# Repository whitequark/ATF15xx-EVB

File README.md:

ATF1502-EVB
===========

*ATF1502-EVB* is a simple and low-cost evaluation board for the [Microchip ATF1502AS](https://www.microchip.com/wwwproducts/en/ATF1502AS) CPLD. It may also be used with ATF1504AS in the TQFP-44 package. It breaks out every I/O pin on a DIP-style package, exposes JTAG on a 6-pin connector, and optionally (with a solder jumper) allows two LEDs to be connected to pins 22 and 23 of the CPLD.

[PCBWay](https://www.pcbway.com/) has sponsored a prototype batch of these boards, and I'm very happy with how they turned out.  (Thanks!) See [this Twitter thread](https://twitter.com/whitequark/status/1238286231433330688) for details.

See also [schematics](ATF1502AS-EVB/Fab/ATF1502AS-EVB.pdf).

ATF1502AS-EVB-PLCC44-COBBLER
============================
The *ATF1502AS-EVB-PLCC44-COBBLER* board features the same ATF1502AS CPLD, but the variant that comes in a PLCC44 package.
The style of the board is a 'cobbler', designed to be easily inserted into a breadboard.
It also features a secondary jtag port designed to be compatible with Olimex ARM-USB-TINY adapters.

See also [schematics](ATF1502AS-EVB-PLCC44-COBBLER/Fab/ATF1502AS-EVB.pdf).

ATF1508AS-EVB-PLCC84
====================
The *ATF1508AS-EVB-PLCC84* board features the bigger ATF1508AS CPLD, this board supports the variant that comes in a PLCC84 package.
It features a secondary jtag port designed to be compatible with Olimex ARM-USB-TINY adapters.

See also [schematics](ATF1508AS-EVB-PLCC84/Fab/ATF1502AS-EVB.pdf).

ATF1502-EVB-PLCC
================
The *ATF1502-EVB-PLCC* board, is a variant for the PLCC-44 package, socketed. It routes the same signals to the headers in the same order and includes the same pin numbers on the silkscreen. These numbers reflect the TQFP-44 pin numbers, but everything is connected correctly to the PLCC-44 package, which has the same 44 signals but in a slightly different order.

License
-------

[CC0](LICENSE-CC0.txt)

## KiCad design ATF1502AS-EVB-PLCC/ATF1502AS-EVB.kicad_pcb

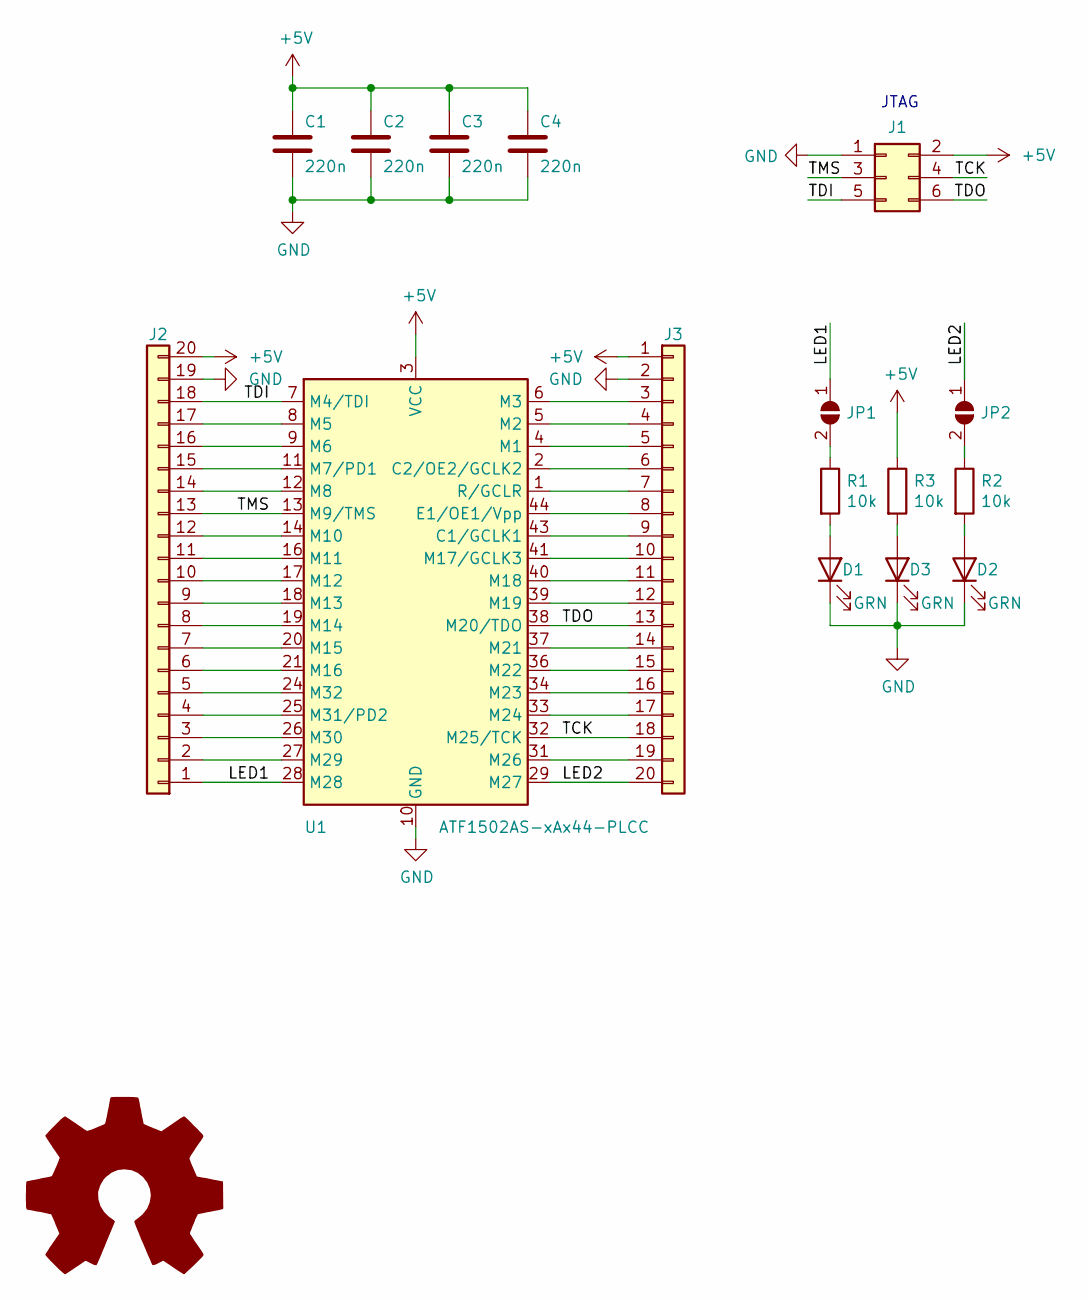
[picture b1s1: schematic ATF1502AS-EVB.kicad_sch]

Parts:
C1, C2, C3, C4: 220n; C_0805_2012Metric_Pad1.15x1.40mm_HandSolder
D1, D2, D3: GRN; LED_0603_1608Metric_Pad1.05x0.95mm_HandSolder; MPN 150060GS75000
J1: VERT; PinHeader_2x03_P2.54mm_Vertical
J2, J3: VERT; PinHeader_1x20_P2.54mm_Vertical_NoSilk
JP1, JP2: DNP; SolderJumper-2_P1.3mm_Open_TrianglePad1.0x1.5mm
R1, R2, R3: 10k; R_0805_2012Metric_Pad1.15x1.40mm_HandSolder
U1: ATF1502AS-xAx44-PLCC; Socket_PLCC_44; MPN ATF1502AS-7AX44

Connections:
+5V: C1.1, C2.1, C3.1, C4.1, J1.2, J2.20, J3.1, R3.1, U1.3 (VCC), U1.15 (VCC), U1.23 (VCC), U1.35 (VCC)
/LED1: J2.1, JP1.1 (A), U1.28 (M28)
/LED2: J3.20, JP2.1 (A), U1.29 (M27)
/TCK: J1.4, J3.18, U1.32 (M25/TCK)
/TDI: J1.5, J2.18, U1.7 (M4/TDI)
/TDO: J1.6, J3.13, U1.38 (M20/TDO)
/TMS: J1.3, J2.13, U1.13 (M9/TMS)
GND: C1.2, C2.2, C3.2, C4.2, D1.1 (K), D2.1 (K), D3.1 (K), J1.1, J2.19, J3.2, U1.10 (GND), U1.22 (GND), U1.30 (GND), U1.42 (GND)
unnamed: D1.2 (A), R1.2
unnamed: D2.2 (A), R2.2
unnamed: D3.2 (A), R3.2
unnamed: J2.2, U1.27 (M29)
unnamed: J2.3, U1.26 (M30)
unnamed: J2.4, U1.25 (M31/PD2)
unnamed: J2.5, U1.24 (M32)
unnamed: J2.6, U1.21 (M16)
unnamed: J2.7, U1.20 (M15)
unnamed: J2.8, U1.19 (M14)
unnamed: J2.9, U1.18 (M13)
unnamed: J2.10, U1.17 (M12)
unnamed: J2.11, U1.16 (M11)
unnamed: J2.12, U1.14 (M10)
unnamed: J2.14, U1.12 (M8)
unnamed: J2.15, U1.11 (M7/PD1)
unnamed: J2.16, U1.9 (M6)
unnamed: J2.17, U1.8 (M5)
unnamed: J3.3, U1.6 (M3)
unnamed: J3.4, U1.5 (M2)
unnamed: J3.5, U1.4 (M1)
unnamed: J3.6, U1.2 (C2/OE2/GCLK2)
unnamed: J3.7, U1.1 (R/GCLR)
unnamed: J3.8, U1.44 (E1/OE1/Vpp)
unnamed: J3.9, U1.43 (C1/GCLK1)
unnamed: J3.10, U1.41 (M17/GCLK3)
unnamed: J3.11, U1.40 (M18)
unnamed: J3.12, U1.39 (M19)
unnamed: J3.14, U1.37 (M21)
unnamed: J3.15, U1.36 (M22)
unnamed: J3.16, U1.34 (M23)
unnamed: J3.17, U1.33 (M24)
unnamed: J3.19, U1.31 (M26)
unnamed: JP1.2 (B), R1.1
unnamed: JP2.2 (B), R2.1

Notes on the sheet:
JTAG

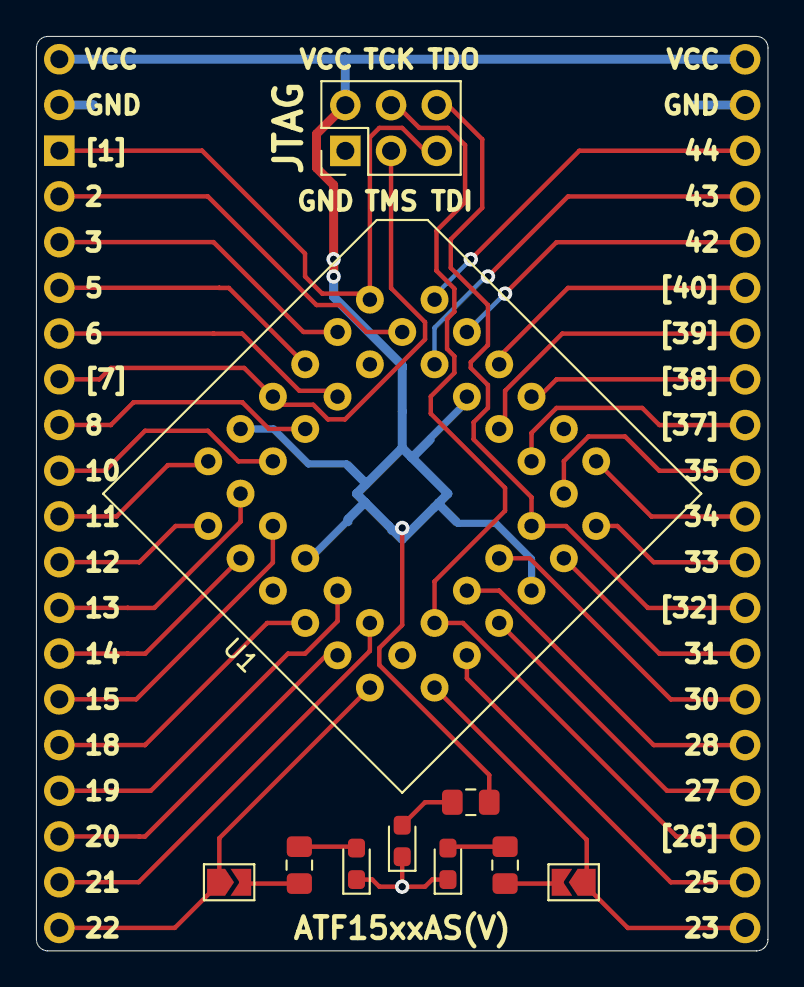
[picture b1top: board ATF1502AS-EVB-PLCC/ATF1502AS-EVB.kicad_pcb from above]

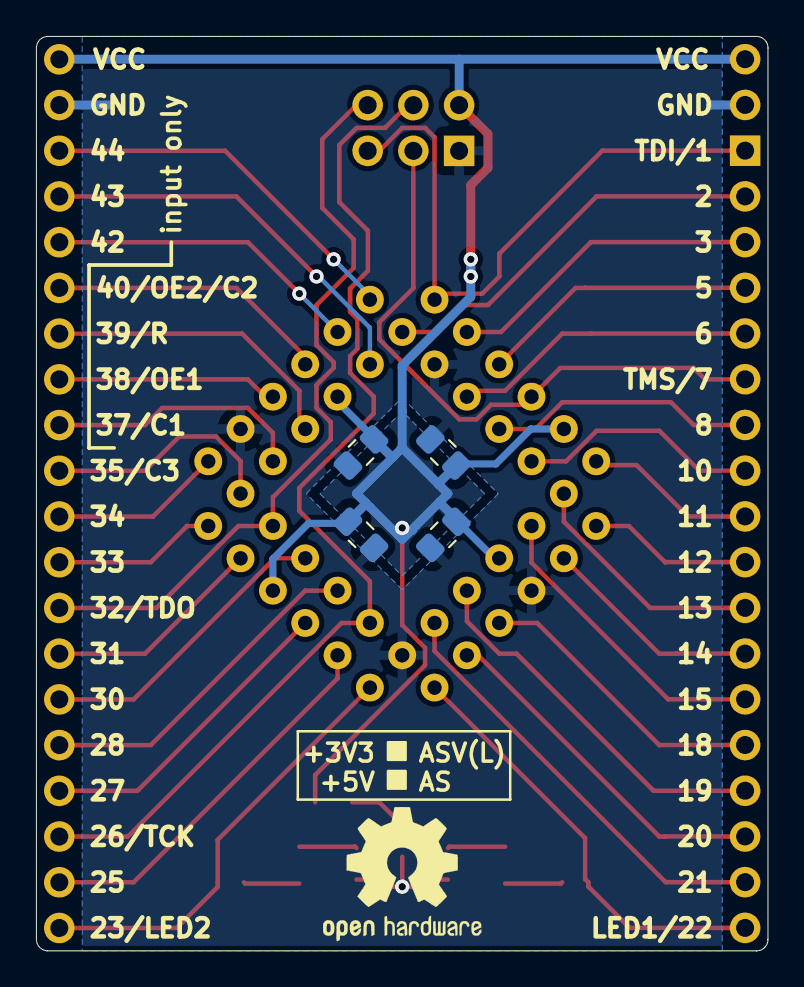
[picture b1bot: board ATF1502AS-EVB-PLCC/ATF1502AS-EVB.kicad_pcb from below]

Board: 2 copper layers, 40.6 x 50.8 mm, 16 parts (6 on the bottom side), 43 nets.

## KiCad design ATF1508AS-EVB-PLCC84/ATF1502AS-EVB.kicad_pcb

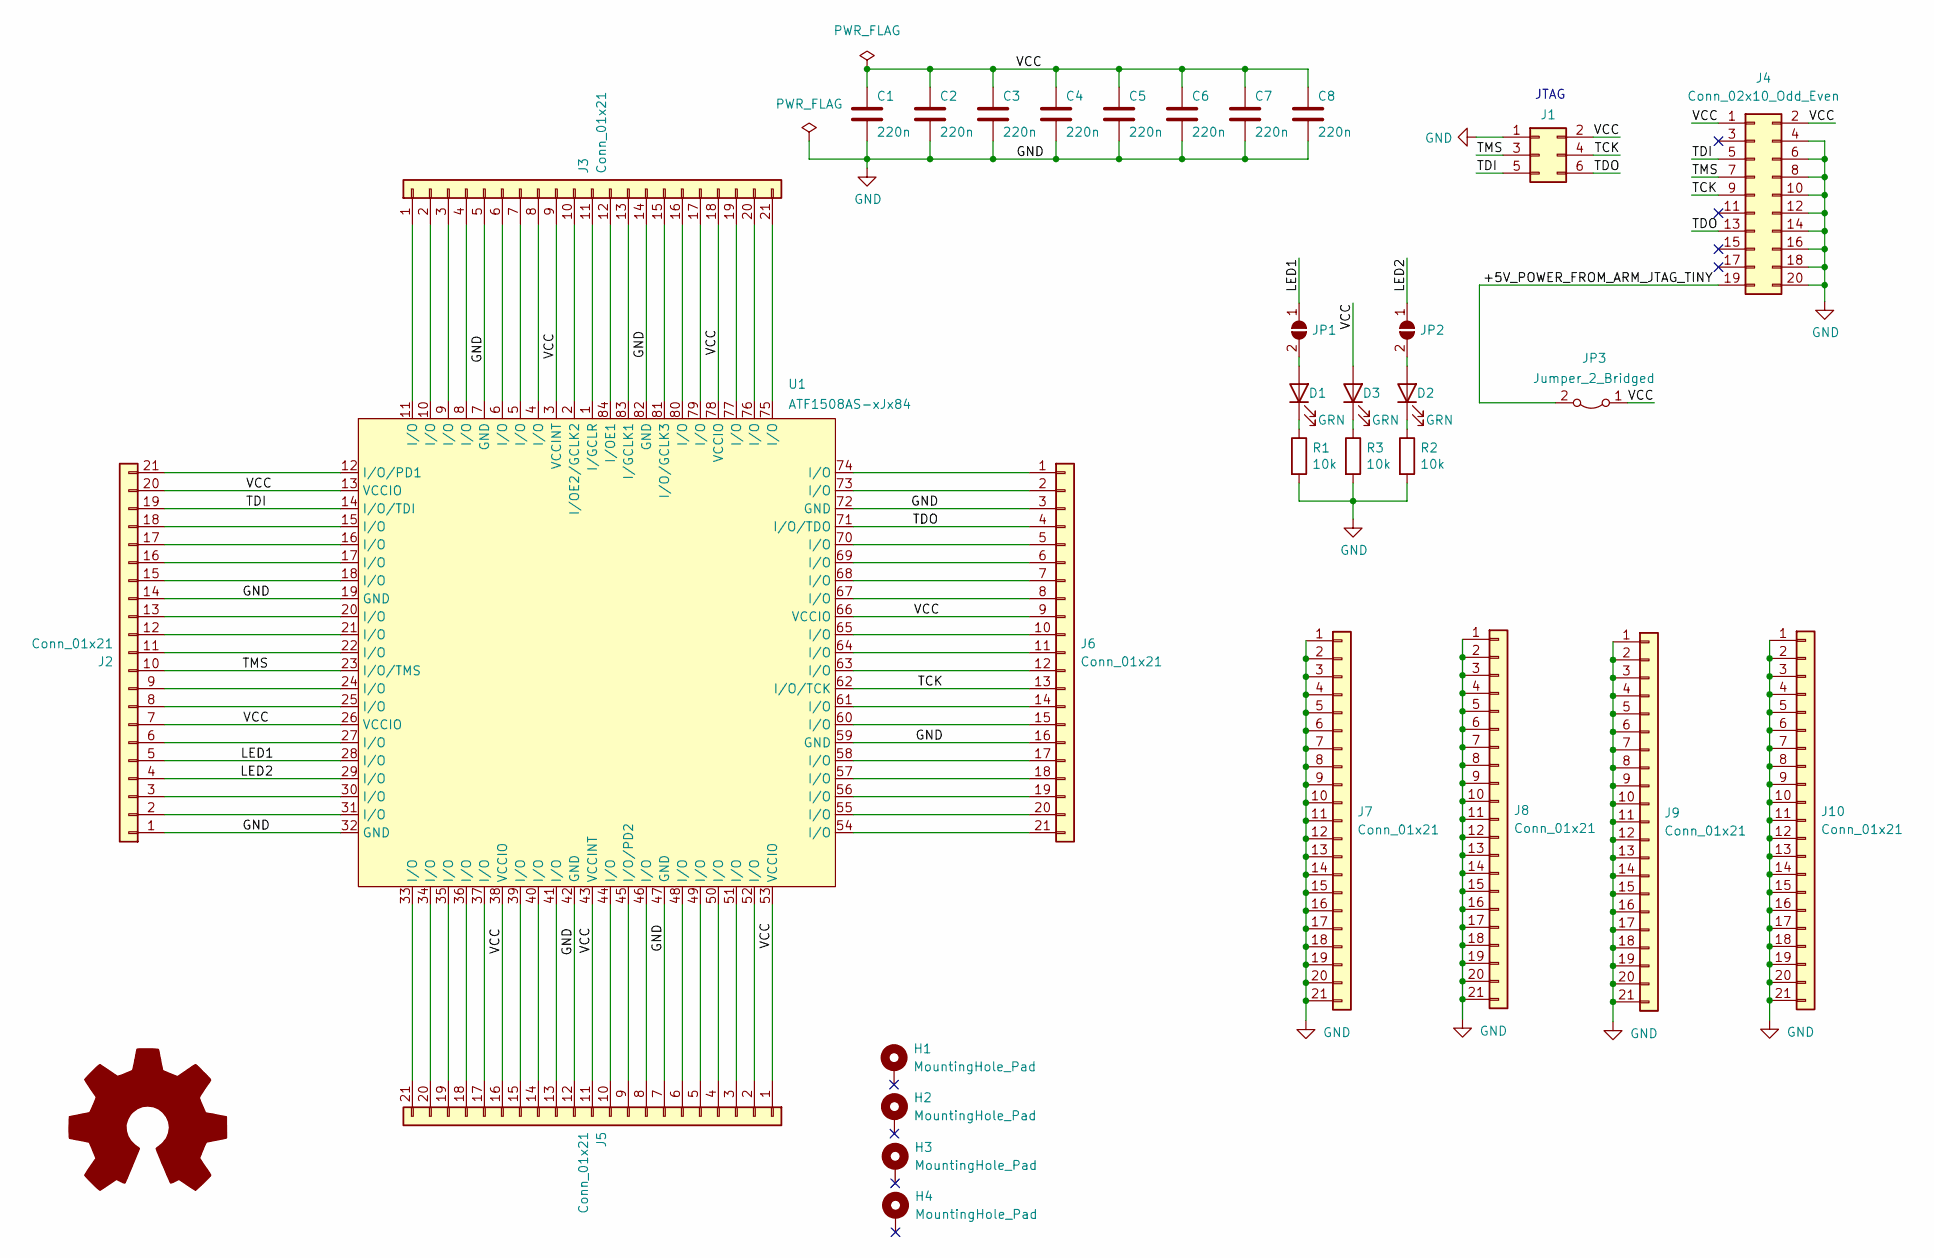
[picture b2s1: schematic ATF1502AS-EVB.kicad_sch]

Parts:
C1, C2, C3, C4, C5, C6, C7, C8: 220n; C_0805_2012Metric_Pad1.18x1.45mm_HandSolder
D1, D2, D3: GRN; LED_0805_2012Metric_Pad1.15x1.40mm_HandSolder; MPN 150060GS75000
H1, H2, H3, H4: MountingHole_Pad; MountingHole_3.2mm_M3_Pad
J1: VERT; PinHeader_2x03_P2.54mm_Vertical
J2, J3, J5, J6, J7, J8, J9, J10: Conn_01x21; PinHeader_1x21_P2.54mm_Vertical
J4: Conn_02x10_Odd_Even; IDC-Header_2x10_P2.54mm_Vertical
JP1, JP2: DNP; SolderJumper-2_P1.3mm_Open_TrianglePad1.0x1.5mm
JP3: Jumper_2_Bridged; PinHeader_1x02_P2.54mm_Vertical
R1, R2, R3: 10k; R_0805_2012Metric_Pad1.15x1.40mm_HandSolder
U1: ATF1508AS-xJx84; PLCC-84-handsold

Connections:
/+5V_POWER_FROM_ARM_JTAG_TINY: J4.19, JP3.2 (B)
/LED1: J2.5, JP1.1 (A), U1.28 (I/O)
/LED2: J2.4, JP2.1 (A), U1.29 (I/O)
/TCK: J1.4, J4.9, J6.13, U1.62 (I/O/TCK)
/TDI: J1.5, J2.19, J4.5, U1.14 (I/O/TDI)
/TDO: J1.6, J4.13, J6.4, U1.71 (I/O/TDO)
/TMS: J1.3, J2.10, J4.7, U1.23 (I/O/TMS)
/VCC: C1.1, C2.1, C3.1, C4.1, C5.1, C6.1, C7.1, C8.1, D3.2 (A), J1.2, J2.7, J2.20, J3.9, J3.18, J4.1, J4.2, J5.1, J5.11, J5.16, J6.9, JP3.1 (A), U1.3 (VCCINT), U1.13 (VCCIO), U1.26 (VCCIO), U1.38 (VCCIO), U1.43 (VCCINT), U1.53 (VCCIO), U1.66 (VCCIO), U1.78 (VCCIO)
GND: C1.2, C2.2, C3.2, C4.2, C5.2, C6.2, C7.2, C8.2, J1.1, J2.1, J2.14, J3.5, J3.14, J4.4, J4.6, J4.8, J4.10, J4.12, J4.14, J4.16, J4.18, J4.20, J5.7, J5.12, J6.3, J6.16, J7.1, J7.2, J7.3, J7.4, J7.5, J7.6, J7.7, J7.8, J7.9, J7.10, J7.11, J7.12, J7.13, J7.14, J7.15, J7.16, J7.17, J7.18, J7.19, J7.20, J7.21, J8.1, J8.2, J8.3, J8.4, J8.5, J8.6, J8.7, J8.8, J8.9, J8.10, J8.11, J8.12, J8.13, J8.14, J8.15, J8.16, J8.17, J8.18, J8.19, J8.20, J8.21, J9.1, J9.2, J9.3, J9.4, J9.5, J9.6, J9.7, J9.8, J9.9, J9.10, J9.11, J9.12, J9.13, J9.14, J9.15, J9.16, J9.17, J9.18, J9.19, J9.20, J9.21, J10.1, J10.2, J10.3, J10.4, J10.5, J10.6, J10.7, J10.8, J10.9, J10.10, J10.11, J10.12, J10.13, J10.14, J10.15, J10.16, J10.17, J10.18, J10.19, J10.20, J10.21, R1.2, R2.2, R3.2, U1.7 (GND), U1.19 (GND), U1.32 (GND), U1.42 (GND), U1.47 (GND), U1.59 (GND), U1.72 (GND), U1.82 (GND)
unnamed: D1.1 (K), R1.1
unnamed: D1.2 (A), JP1.2 (B)
unnamed: D2.1 (K), R2.1
unnamed: D2.2 (A), JP2.2 (B)
unnamed: D3.1 (K), R3.1
unnamed: J2.2, U1.31 (I/O)
unnamed: J2.3, U1.30 (I/O)
unnamed: J2.6, U1.27 (I/O)
unnamed: J2.8, U1.25 (I/O)
unnamed: J2.9, U1.24 (I/O)
unnamed: J2.11, U1.22 (I/O)
unnamed: J2.12, U1.21 (I/O)
unnamed: J2.13, U1.20 (I/O)
unnamed: J2.15, U1.18 (I/O)
unnamed: J2.16, U1.17 (I/O)
unnamed: J2.17, U1.16 (I/O)
unnamed: J2.18, U1.15 (I/O)
unnamed: J2.21, U1.12 (I/O/PD1)
unnamed: J3.1, U1.11 (I/O)
unnamed: J3.2, U1.10 (I/O)
unnamed: J3.3, U1.9 (I/O)
unnamed: J3.4, U1.8 (I/O)
unnamed: J3.6, U1.6 (I/O)
unnamed: J3.7, U1.5 (I/O)
unnamed: J3.8, U1.4 (I/O)
unnamed: J3.10, U1.2 (I/OE2/GCLK2)
unnamed: J3.11, U1.1 (I/GCLR)
unnamed: J3.12, U1.84 (I/OE1)
unnamed: J3.13, U1.83 (I/GCLK1)
unnamed: J3.15, U1.81 (I/O/GCLK3)
unnamed: J3.16, U1.80 (I/O)
unnamed: J3.17, U1.79 (I/O)
unnamed: J3.19, U1.77 (I/O)
unnamed: J3.20, U1.76 (I/O)
unnamed: J3.21, U1.75 (I/O)
unnamed: J5.2, U1.52 (I/O)
unnamed: J5.3, U1.51 (I/O)
unnamed: J5.4, U1.50 (I/O)
unnamed: J5.5, U1.49 (I/O)
unnamed: J5.6, U1.48 (I/O)
unnamed: J5.8, U1.46 (I/O)
unnamed: J5.9, U1.45 (I/O/PD2)
unnamed: J5.10, U1.44 (I/O)
unnamed: J5.13, U1.41 (I/O)
unnamed: J5.14, U1.40 (I/O)
unnamed: J5.15, U1.39 (I/O)
unnamed: J5.17, U1.37 (I/O)
unnamed: J5.18, U1.36 (I/O)
unnamed: J5.19, U1.35 (I/O)
unnamed: J5.20, U1.34 (I/O)
unnamed: J5.21, U1.33 (I/O)
unnamed: J6.1, U1.74 (I/O)
unnamed: J6.2, U1.73 (I/O)
unnamed: J6.5, U1.70 (I/O)
unnamed: J6.6, U1.69 (I/O)
unnamed: J6.7, U1.68 (I/O)
unnamed: J6.8, U1.67 (I/O)
unnamed: J6.10, U1.65 (I/O)
unnamed: J6.11, U1.64 (I/O)
unnamed: J6.12, U1.63 (I/O)
unnamed: J6.14, U1.61 (I/O)
unnamed: J6.15, U1.60 (I/O)
unnamed: J6.17, U1.58 (I/O)
unnamed: J6.18, U1.57 (I/O)
unnamed: J6.19, U1.56 (I/O)
unnamed: J6.20, U1.55 (I/O)
unnamed: J6.21, U1.54 (I/O)

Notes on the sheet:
JTAG

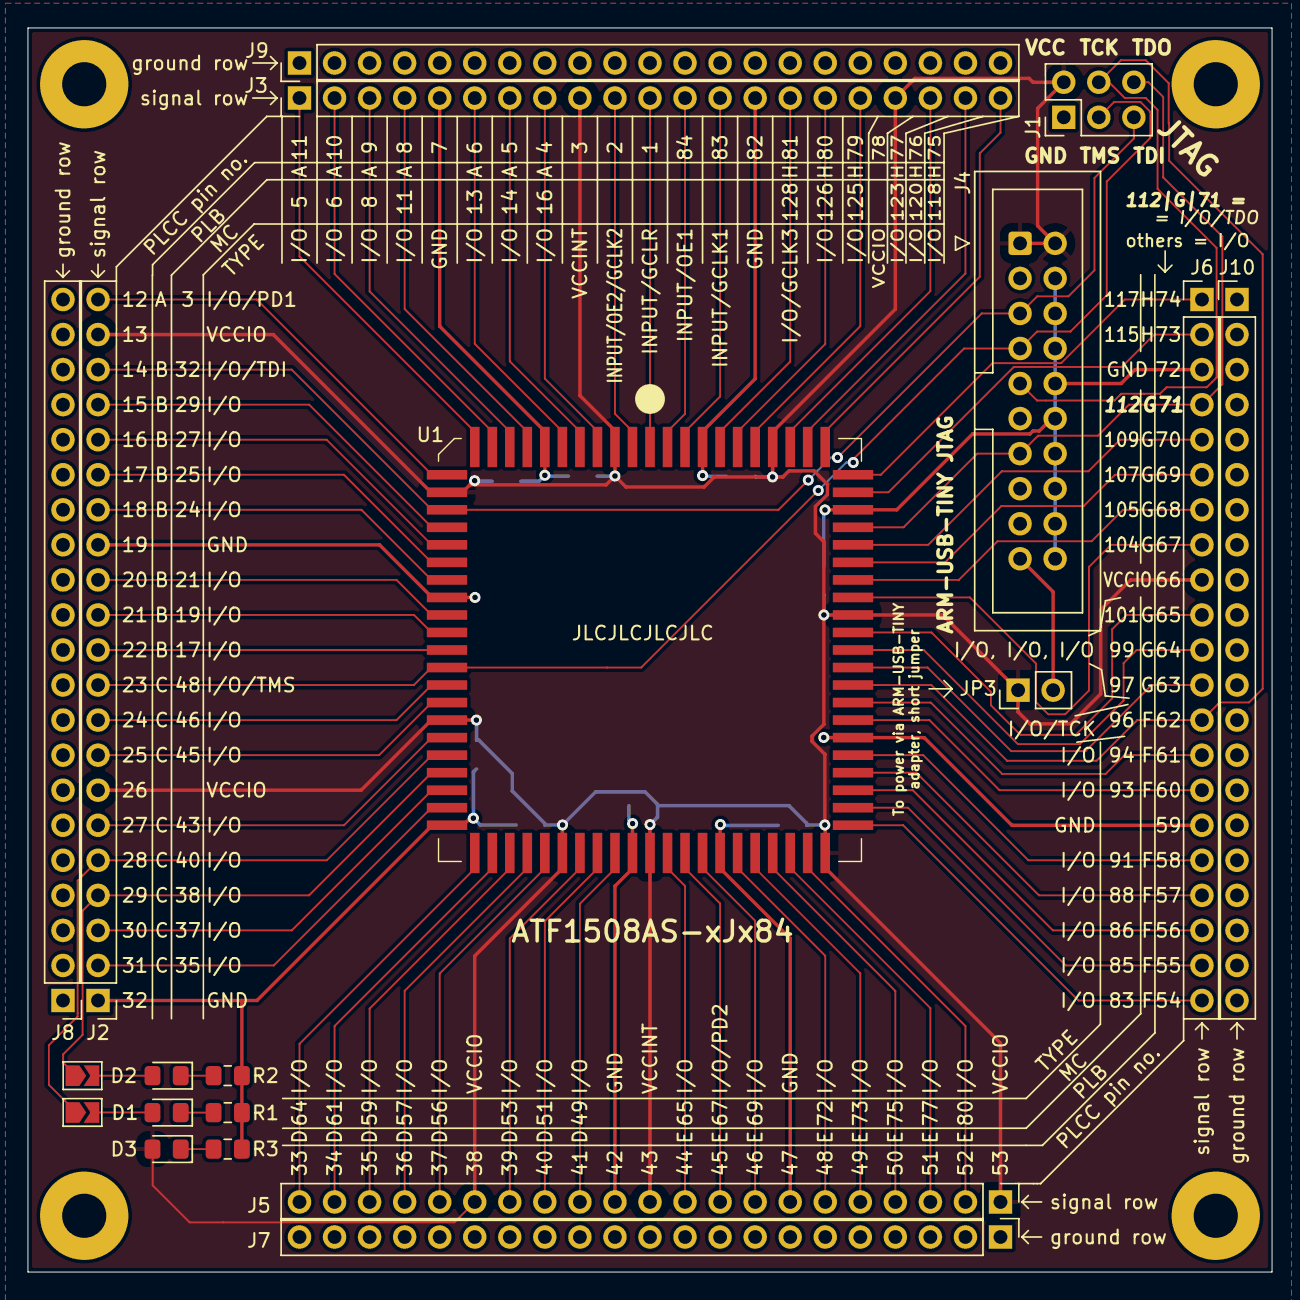
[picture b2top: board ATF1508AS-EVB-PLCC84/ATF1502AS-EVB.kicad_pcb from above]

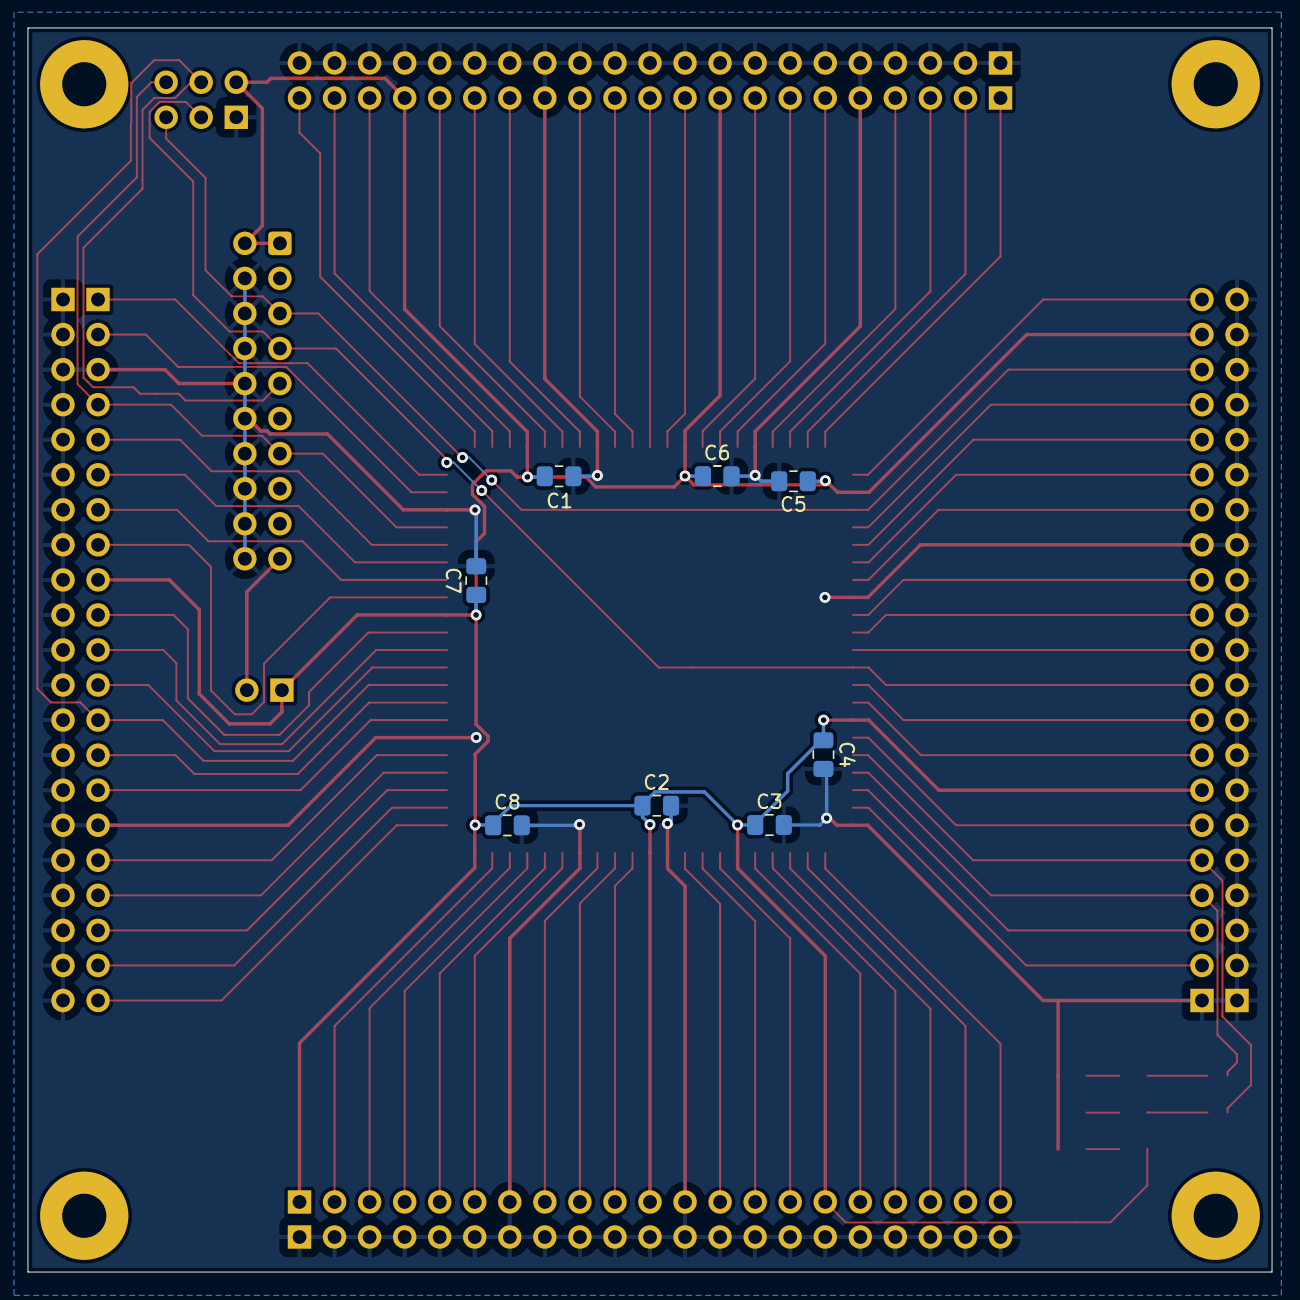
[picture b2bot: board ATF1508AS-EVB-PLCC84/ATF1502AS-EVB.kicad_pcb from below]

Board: 2 copper layers, 90.2 x 90.2 mm, 32 parts (8 on the bottom side), 76 nets.

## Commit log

2019-12-12 Add ATF1502AS-EVB.
2019-12-12 ATF1502AS-EVB: show LED<>pin correspondence on silk.
2019-12-12 ATF1502AS-EVB: improve symmetry further.
2019-12-15 Update for upstream changes.
2019-12-16 ATF1502AS-EVB: final changes for fab.
2019-12-16 ATF1502AS-EVB: add fab outputs.
2019-12-22 Add README, relicense to CC0.
    There's no meaningful difference between BSD0 and CC0, but it seems
    ambiguous to use BSD0 for PCBs when it specifically says "software".
2021-01-22 Modifies silkscreen for 3v3 and 5v parts
2021-01-22 Modify silkscreen for 3v3 and 5v parts.
2022-12-23 prl files should not be stored in the git repo
2024-02-17 Extended gitignore
2024-02-17 Added ATF1508AS-EVB-PLCC84
2024-02-17 Added ATF1502AS-EVB-PLCC44-COBBLER
2024-02-17 Extend `.gitignore`.
2024-02-17 ATF1502AS-EVB-PLCC: Provide a PLCC Variant EVB
    - Created a new symbol for the PLCC version which has a different pinout
    - Widened the board to allow for the larger PLCC socket.
    - The silkscreen numbers and header pin order matches that of the TQFP
    version of the board, but everything is routed to the correct TQFP pins.
